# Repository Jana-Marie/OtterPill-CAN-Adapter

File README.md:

# OtterPill-CAN-Adapter

CAN-adapter for the [OtterPill](https://github.com/Jan--Henrik/OtterPill) running [candleLight firmware](https://github.com/candle-usb/candleLight_fw).

**Note: does not work properly when no 3.3V CAN tranceiver is assembled**

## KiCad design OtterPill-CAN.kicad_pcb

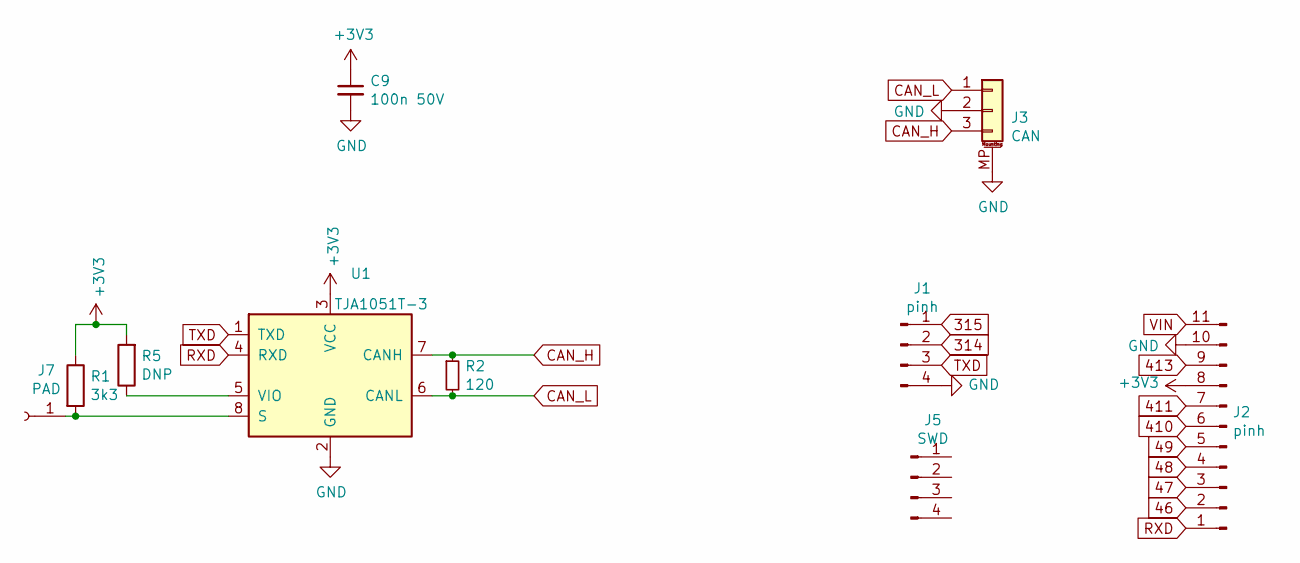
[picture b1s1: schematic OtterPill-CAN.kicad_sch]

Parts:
C9: 100n 50V; C_0603_1608Metric
J1: pinh; PinHeader_1x04_P2.54mm_Vertical_NOSILK
J2: pinh; PinHeader_1x11_P2.54mm_Vertical_NOSILK
J3: CAN; JST_XH_3Pin_short_pads
J5: SWD; PinHeader_1x04_P2.54mm_Vertical_HOLESONLY
J7: PAD; PinHeader_1x01_P2.54mm_Vertical_NOSILK
R1: 3k3; R_0603_1608Metric
R2: 120; R_0603_1608Metric
R5: DNP; R_0603_1608Metric
U1: TJA1051T-3; SOIC-8_3.9x4.9mm_P1.27mm

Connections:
46: J2.2
47: J2.3
48: J2.4
49: J2.5
314: J1.2
315: J1.1
410: J2.6
411: J2.7
413: J2.9
+3V3: C9.1, J2.8, R1.1, R5.2, U1.3 (VCC)
CAN_H: J3.3, R2.1, U1.7 (CANH)
CAN_L: J3.1, R2.2, U1.6 (CANL)
GND: C9.2, J1.4, J2.10, J3.2, J3.MP (MountPin), U1.2 (GND)
unnamed: J7.1, R1.2, U1.8 (S)
unnamed: R5.1, U1.5 (VIO)
RXD: J2.1, U1.4 (RXD)
TXD: J1.3, U1.1 (TXD)
VIN: J2.11

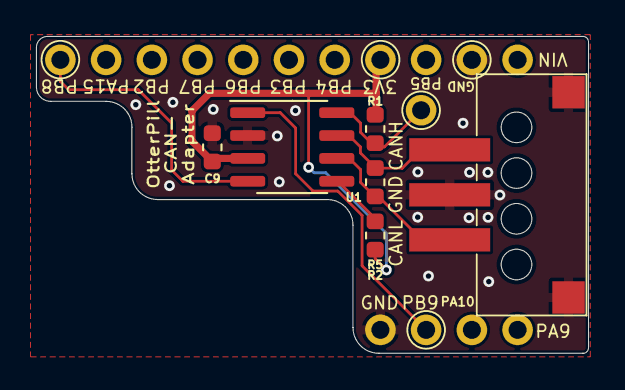
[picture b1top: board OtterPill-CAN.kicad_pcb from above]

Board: 2 copper layers, 30.7 x 17.6 mm, 10 parts (1 on the bottom side), 8 nets.

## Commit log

2019-10-24 message
2019-10-24 added README
2019-10-24 finalized schematic
2019-10-26 finalized layout
2019-10-27 added image
2019-10-27 changed corner radius
2019-11-18 added gerber
2022-01-18 updated to kicad 6
